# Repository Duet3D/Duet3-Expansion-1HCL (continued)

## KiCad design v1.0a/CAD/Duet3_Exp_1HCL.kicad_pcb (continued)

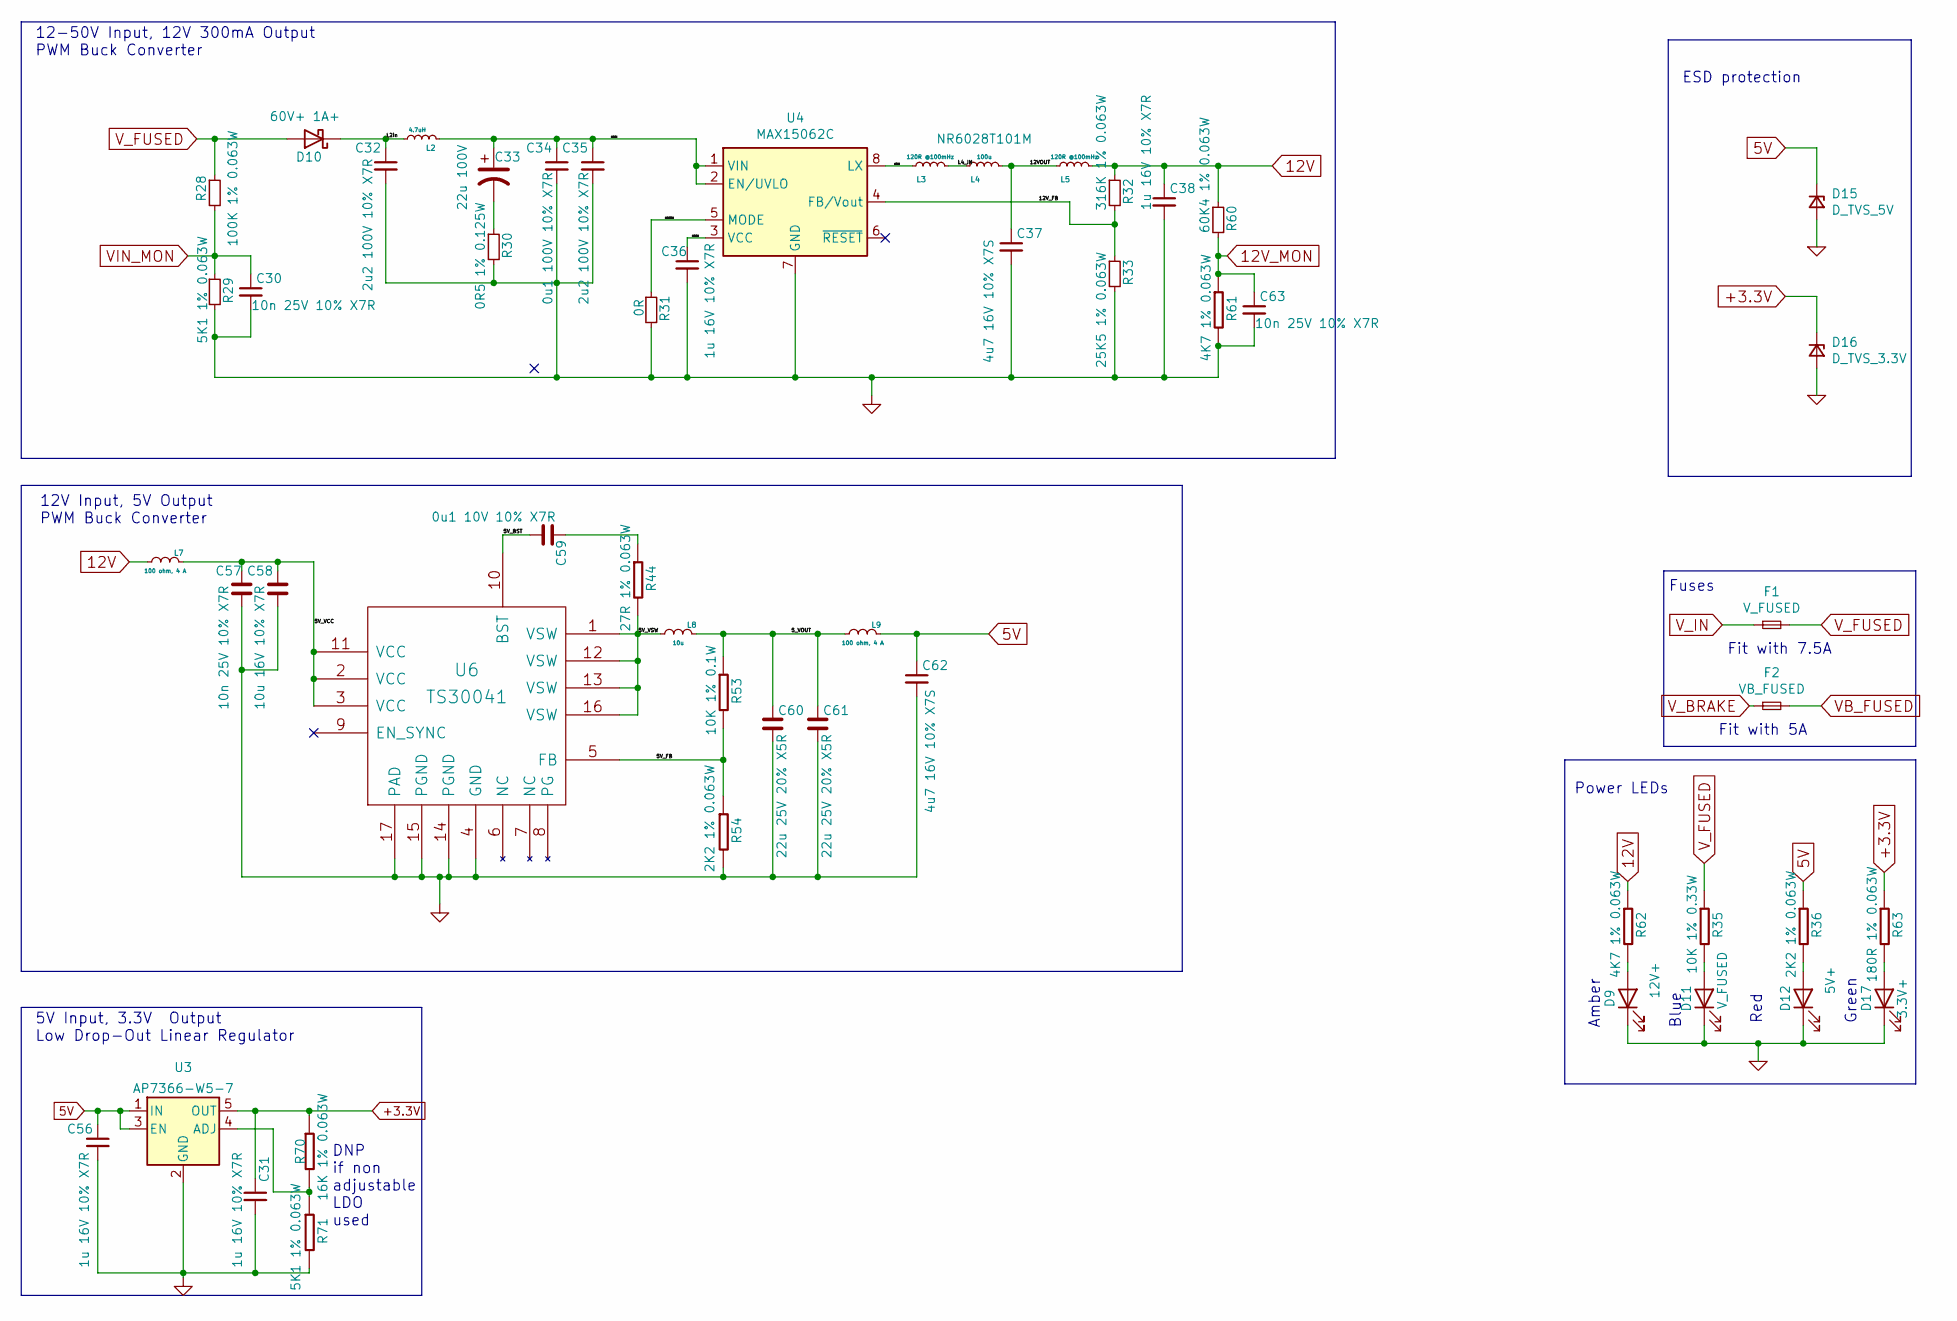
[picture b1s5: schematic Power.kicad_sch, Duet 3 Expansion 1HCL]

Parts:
C30, C57, C63: 10n 25V 10% X7R; C_0402_1005Metric_Wbry; Part Number CL05B103KA5VPNC
C31, C36, C38, C56: 1u 16V 10% X7R; C_0603_1608Metric_Wbry; Part Number CL10B105KO8NNNC
C32, C35: 2u2 100V 10% X7R; C_1210_3225Metric; Part Number CL32B225KCJSNNE
C33: 22u 100V; CP_Elec_8x10; Part Number EEE-2AA220UP or similar
C34: 0u1 100V 10% X7R; C_0603_1608Metric_Wbry; Part Number HMK107B7104MA-T or similar
C37, C62: 4u7 16V 10% X7S; C_1206_3216Metric; Part Number GRM21BR71C475KE51K
C58: 10u 16V 10% X7R; C_0805_2012Metric; Part Number CL21B106KOQNNNE
C59: 0u1 10V 10% X7R; C_0402_1005Metric_Wbry; Part Number CL05B104KP5NNNC
C60, C61: 22u 25V 20% X5R; C_0805_2012Metric; Part Number GRM21BR61E226ME44L
D9: 12V+; LED_0603_1608Metric; Part Number 150060AS75000 or equivalent Amber
D10: 60V+ 1A+; D_SMF; Part Number SS1FH10-M3/H or equivalent
D11: V_FUSED; LED_0603_1608Metric; Part Number 150060BS75000 or equivalent Blue
D12: 5V+; LED_0603_1608Metric; Part Number 150060RS75000 or equivalent Red
D15: D_TVS_5V; DFN1610-2L; Part Number 824032815 or 824031815
D16: D_TVS_3.3V; DFN1610-2L; Part Number 824032813
D17: 3.3V+; LED_0603_1608Metric; Part Number 150060VS75000 or equivalent Green
F1: V_FUSED; MCCQ-122-minibladefuseholder; Part Number Fit with 5A Fuse
F2: VB_FUSED; MCCQ-122-minibladefuseholder; Part Number Fit with 5A Fuse
L2: 4.7uH; L_0805_2012Metric; Part Number MBKK2012T4R7M or CB2012T4R7M or similar
L3, L5: 120R @100mHz; L_0402_1005Metric; Part Number 7427927311 or similar
L4: 100u; L_Taiyo-Yuden_NR-60xx; Rating >0.5A, >0.6A saturation, shielded, <0R8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; Part Number NR6028T101M
L7, L9: 100 ohm, 4 A; L_0805_2012Metric; Part Number 742792025 or MPZ2012S101A or similar
L8: 10u; L_Wuerth_7440405xxxx; Part Number 74404054100 or NR5040T100M
R28: 100K 1% 0.063W; R_0402_1005Metric_Wbry; Part Number RMCF0402FT100K
R29, R71: 5K1 1% 0.063W; R_0402_1005Metric_Wbry; Part Number RMCF0402FT5K10
R30: 0R5 1% 0.125W; R_0402_1005Metric_Wbry; Part Number CSR0402FKR500
R31: 0R; R_0402_1005Metric_Wbry; Part Number RMCF0402ZT0R00
R32: 316K 1% 0.063W; R_0402_1005Metric_Wbry; Part Number RC0402FR-07316KL
R33: 25K5 1% 0.063W; R_0402_1005Metric_Wbry; Part Number AC0402FR-0725K5L
R35: 10K 1% 0.33W; R_0805_2012Metric; Part Number CRGH0805F10K
R36, R54: 2K2 1% 0.063W; R_0402_1005Metric_Wbry; Part Number RK73H1ETTP2201F
R44: 27R 1% 0.063W; R_0402_1005Metric_Wbry; Rating 0.1W+; Part Number CRGCQ0402F27R
R53: 10K 1% 0.1W; R_0402_1005Metric_Wbry; Part Number RK73H1ETTP1002F
R60: 60K4 1% 0.063W; R_0402_1005Metric_Wbry; Part Number RMCF0402FT60K4
R61, R62: 4K7 1% 0.063W; R_0402_1005Metric_Wbry; Part Number RK73H1ETTP4701F
R63: 180R 1% 0.063W; R_0402_1005Metric_Wbry; Part Number RMCF0402FT180R
R70: 16K 1% 0.063W; R_0402_1005Metric_Wbry; Part Number RMCF0402FT16K0
U3: AP7366-W5-7; SOT-23-5; Part Number AP7366-W5-7
U4: MAX15062C; DFN-8_2x2mm_P0.5mm; Part Number MAX15062C
U6: TS30041; QFN-16-1EP_3x3mm_P0.5mm_EP1.8x1.8mm_ThermalVias; Part Number TS30041-M000QFNR

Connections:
5V: C56.1, C62.1, D15.1 (K), L9.1 (A), R36.1, U3.1 (IN), U3.3 (EN); also elsewhere on the board
12V: C38.1, L5.2, L7.2 (B), R32.1, R60.1, R62.1; also elsewhere on the board
12V_MON: C63.1, R60.2, R61.1; also elsewhere on the board
+3.3V: C31.1, D16.1 (K), R63.1, R70.1, U3.5 (OUT); also elsewhere on the board
/Power/5V_BST: C59.2, U6.10 (BST)
/Power/5V_FB: R53.2, R54.1, U6.5 (FB)
/Power/5V_VCC: C57.1, C58.1, L7.1 (A), U6.2 (VCC), U6.3 (VCC), U6.11 (VCC)
/Power/5V_VSW: L8.2 (B), R44.2, U6.1 (VSW), U6.12 (VSW), U6.13 (VSW), U6.16 (VSW)
/Power/5_VOUT: C60.1, C61.1, L8.1 (A), L9.2 (B), R53.1
/Power/12LX: L3.1, U4.8 (LX)
/Power/12MODE: R31.1, U4.5 (MODE)
/Power/12VCC: C36.1, U4.3 (VCC)
/Power/12VIN: C33.1, C34.1, C35.1, L2.2, U4.1 (VIN), U4.2 (EN/UVLO)
/Power/12VOUT: C37.1, L4.2, L5.1
/Power/12V_FB: R32.2, R33.1, U4.4 (FB/Vout)
/Power/L2in: C32.1, D10.1 (K), L2.1
/Power/L4_IN: L3.2, L4.1
GND: C30.2, C31.2, C32.2, C34.2, C35.2, C36.2, C37.2, C38.2, C56.2, C57.2, C58.2, C60.2, C61.2, C62.2, C63.2, D9.1 (K), D11.1 (K), D12.1 (K), D15.2 (A), D16.2 (A), D17.1 (K), R29.2, R30.2, R31.2, R33.2, R54.2, R61.2, R71.2, U3.2 (GND), U4.7 (GND), U6.4 (GND), U6.14 (PGND), U6.15 (PGND), U6.17 (PAD); also elsewhere on the board
unnamed: C33.2, R30.1
unnamed: C59.1, R44.1
unnamed: D9.2 (A), R62.2
unnamed: D11.2 (A), R35.2
unnamed: D12.2 (A), R36.2
unnamed: D17.2 (A), R63.2
unnamed: R70.2, R71.1, U3.4 (ADJ)
VB_FUSED: F2.2; also elsewhere on the board
VIN_MON: C30.1, R28.2, R29.1; also elsewhere on the board
V_BRAKE: F2.1; also elsewhere on the board
V_FUSED: D10.2 (A), F1.2, R28.1, R35.1; also elsewhere on the board
V_IN: F1.1; also elsewhere on the board

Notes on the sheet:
Fit with 7.5A
5V Input, 3.3V Output Low Drop-Out Linear Regulator
12V Input, 5V Output PWM Buck Converter
Power LEDs
Fit with 5A
Fuses
Amber
12-50V Input, 12V 300mA Output PWM Buck Converter
ESD protection
DNP if non adjustable LDO used
Blue
Red
Green

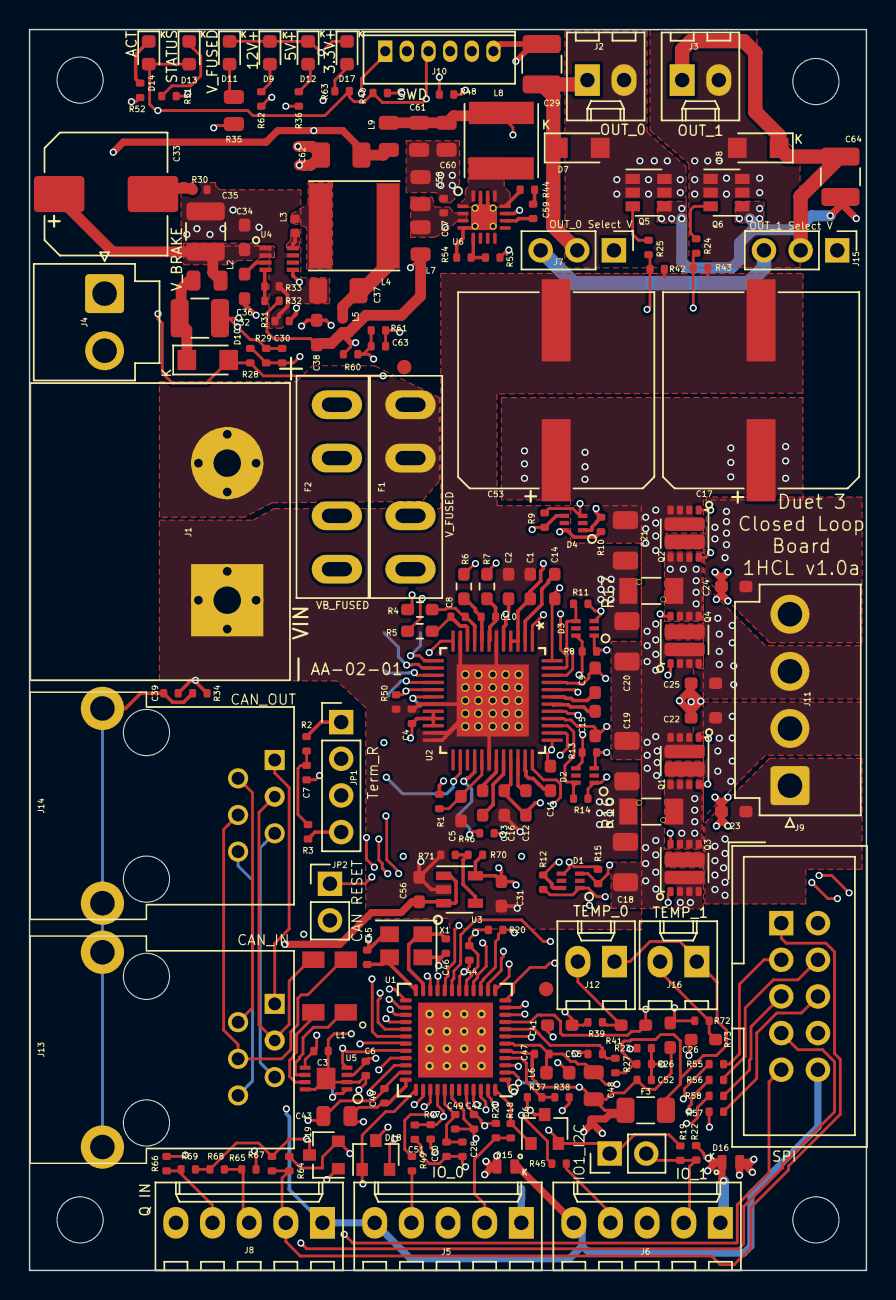
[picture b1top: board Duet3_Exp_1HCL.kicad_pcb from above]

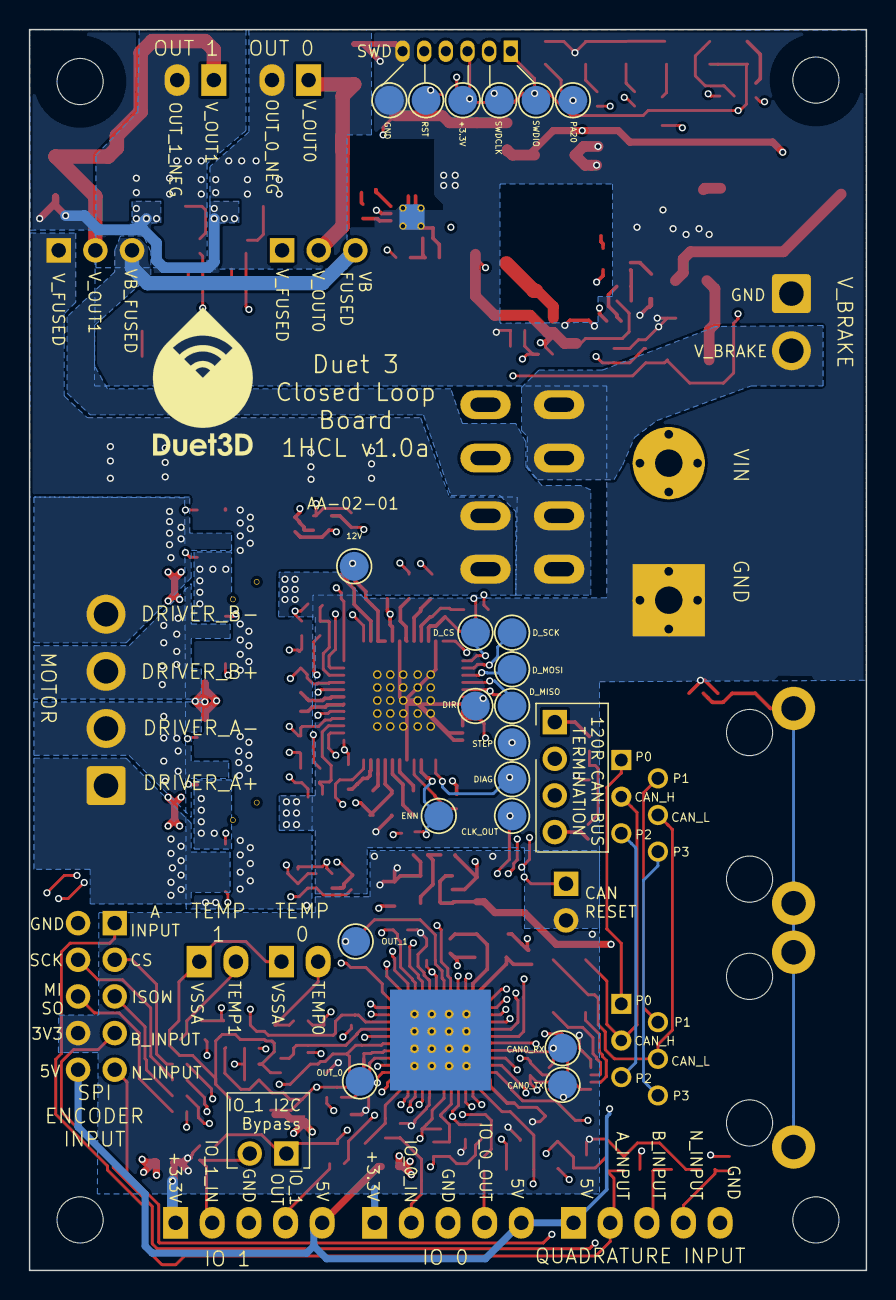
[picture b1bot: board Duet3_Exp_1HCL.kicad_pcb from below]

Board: 4 copper layers, 58.0 x 86.0 mm, 224 parts (21 on the bottom side), 143 nets.

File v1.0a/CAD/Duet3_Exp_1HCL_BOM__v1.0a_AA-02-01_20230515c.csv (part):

"Source:","G:\My Drive\Duet\Duet3\Duet3 Expansion 1HCL\Duet3_Expansion_1HCL_v1.0a-AA-02-01\Duet3_Exp_1HCL.kicad_sch"
"Date:","15/05/2023 18:52:26"
"Tool:","Eeschema (6.0.0)"
"Generator:","C:\Program Files\KiCad\bin\scripting\plugins/bom_csv_grouped_by_value_d3d.py"
"Component Count:","204"

"Collated Components:"

"Item","Value","Qty","LibPart","Footprint","Reference(s)","Datasheet","Frequency","Part Number","Rating"
"1","2u2 16V 10% X5R","4","Device:C_Small","Capacitor_SMD:C_0603_1608Metric_Wbry","C1, C2, C26, C41","~","","CL10A225KO8NNNC",""
"2","0u1 10V 10% X7R","8","Device:C_Small","Capacitor_SMD:C_0402_1005Metric_Wbry","C3, C4, C6, C40, C42, C44, C47, C49","~","","CL05B104KP5NNNC",""
"3","470n 16V 10% X7R","1","Device:C_Small","Capacitor_SMD:C_0603_1608Metric_Wbry","C5","~","","CL10B474KO8NNNC",""
"4","10n 25V 10% X7R","5","Device:C_Small","Capacitor_SMD:C_0402_1005Metric_Wbry","C7, C30, C39, C51, C63","~","","CL05B103KA5VPNC",""
"5","2n2 50V 10% X7R","2","Device:C_Small","Capacitor_SMD:C_0402_1005Metric_Wbry","C8, C10","~","","GCM155R71H222KA37D",""
"6","220n 16V 10% X7R","4","Device:C_Small","Capacitor_SMD:C_0603_1608Metric_Wbry","C9, C11, C14, C15","~","","CL10B224KO8NNNC",""
"7","0u1 50V  10% X7R","1","Device:C_Small","Capacitor_SMD:C_0603_1608Metric_Wbry","C12","~","","CL10B104KB8NNNC",""
"8","22n 100V 10% X7R","1","Device:C_Small","Capacitor_SMD:C_0603_1608Metric_Wbry","C13","~","","C0603C223K1RACTU",""
"9","0u1 100V 10% X7R","2","Device:C_Small","Capacitor_SMD:C_0603_1608Metric_Wbry","C16, C34","~","","HMK107B7104MA-T or similar",""
"10","220u 63V","2","Device:CP1_Small","Capacitor_SMD:CP_Elec_12.5x14","C17, C53","","","865060762009",""
"11","220n 100V 10% X7R","4","Device:C_Small","Capacitor_SMD:C_1206_3216Metric","C18, C19, C20, C21","~","","C3216X7R2A224K115AA",""
"12","1n 100V 10% X7R","4","Device:C_Small","Capacitor_SMD:C_0603_1608Metric_Wbry","C22, C23, C24, C25","~","","CGA3E2X7R2A102K080AA",""
"13","2u2 6.3V 10% X7R","4","Device:C_Small","Capacitor_SMD:C_0402_1005Metric_Wbry","C28, C50, C52, C55","~","","CC0603KRX7R5BB225",""
"14","2u2 100V 10% X7R","4","Device:C_Small","Capacitor_SMD:C_1210_3225Metric","C29, C32, C35, C64","~","","CL32B225KCJSNNE",""
"15","1u 16V 10% X7R","4","Device:C_Small","Capacitor_SMD:C_0603_1608Metric_Wbry","C31, C36, C38, C56","~","","CL10B105KO8NNNC",""
"16","22u 100V","1","Device:CP1","Capacitor_SMD:CP_Elec_8x10","C33","","","EEE-2AA220UP or similar",""
"17","4u7 16V 10% X7S","2","Device:C_Small","Capacitor_SMD:C_1206_3216Metric","C37, C62","~","","GRM21BR71C475KE51K",""
"18","10u 16V 10% X7R","2","Device:C_Small","Capacitor_SMD:C_0805_2012Metric","C43, C48","~","","CL21B106KOQNNNE",""
"19","22p 16V 5% C0G,NP0","2","Device:C_Small","Capacitor_SMD:C_0402_1005Metric_Wbry","C45, C46","~","","C0402C220J4GACTU",""
"20","10n 25V 10% X7R","1","Duet3:C_SMALL","Capacitor_SMD:C_0402_1005Metric_Wbry","C57","","","CL05B103KA5VPNC",""
"21","10u 16V 10% X7R","1","Duet3:C_SMALL","Capacitor_SMD:C_0805_2012Metric","C58","","","CL21B106KOQNNNE",""
"22","0u1 10V 10% X7R","1","Duet3:C_SMALL","Capacitor_SMD:C_0402_1005Metric_Wbry","C59","","","CL05B104KP5NNNC",""
"23","22u 25V 20% X5R","2","Duet3:C_SMALL","Capacitor_SMD:C_0805_2012Metric","C60, C61","","","GRM21BR61E226ME44L",""
"24","BAT40V","4","Diode:BAT40V","Package_TO_SOT_SMD:SOT-563","D1, D2, D3, D4","","","BAT40V-7",""
"25","BAT54C","3","Diode:BAT54C","Package_TO_SOT_SMD:SOT-23","D6, D18, D19","http://www.diodes.com/_files/datasheets/ds11005.pdf","","BAT54CLT1G",""
"26","60V+ 1A+","3","Device:D_Schottky","Diode_SMD:D_SMF","D7, D8, D10","~","","SS1FH10-M3/H or equivalent",""
"27","12V+","1","Device:LED","LED_SMD:LED_0603_1608Metric","D9","~","","150060AS75000 or equivalent Amber",""
"28","V_FUSED","1","Device:LED","LED_SMD:LED_0603_1608Metric","D11","~","","150060BS75000  or equivalent Blue",""
"29","5V+","1","Device:LED","LED_SMD:LED_0603_1608Metric","D12","~","","150060RS75000 or equivalent Red",""
"30","STATUS","1","Device:LED","LED_SMD:LED_0603_1608Metric","D13","~","","150060RS75000 or equivalent Red",""
"31","ACT","1","Device:LED","LED_SMD:LED_0603_1608Metric","D14","~","","150060VS75000  or equivalent Green",""
"32","D_TVS_5V","1","Device:D_Zener_Small","Diode_SMD:DFN1610-2L","D15","~","","824032815 or 824031815",""
"33","D_TVS_3.3V","1","Device:D_Zener_Small","Diode_SMD:DFN1610-2L","D16","~","","824032813",""
"34","3.3V+","1","Device:LED","LED_SMD:LED_0603_1608Metric","D17","~","","150060VS75000  or equivalent Green",""
"35","V_FUSED","1","Device:Fuse_Small","complib:MCCQ-122-minibladefuseholder","F1","~","","Fit with 5A Fuse",""
"36","VB_FUSED","1","Device:Fuse_Small","complib:MCCQ-122-minibladefuseholder","F2","~","","Fit with 5A Fuse",""
"37","VSSA FUSE","1","Device:Fuse","Fuse:Fuse_1206_3216Metric","F3","~","","0ZCJ0020FF2E",""
"38","VIN","1","Connector_Generic:Conn_01x02","complib:screwt-barrier-9.5mm-1x2","J1","~",""," HB950-9.50-2P",""
"39","OUT_0","1","Connector_Generic:Conn_01x02","Connector_Molex:Wurth_61900211121-1x02_P2.54mm_Vertical-(Molex_KK-254_AE-6410-02Acompatible)","J2","~","","61900211121",""
"40","OUT_1","1","Connector_Generic:Conn_01x02","Connector_Molex:Wurth_61900211121-1x02_P2.54mm_Vertical-(Molex_KK-254_AE-6410-02Acompatible)","J3","~","","61900211121",""
"41","V_BRAKE","1","Connector_Generic:Conn_01x02","Connector_JST:JST_VH_B2P-VH_1x02_P3.96mm_Vertical","J4","~","","B2P-VH(LF)(SN)",""
"42","IO_0","1","Connector_Generic:Conn_01x05","Connector_Molex:Wurth_61900511121-1x05_P2.54mm_Vertical(Molex_KK-254_AE-6410-05A_Compatibe)","J5","~","","61900511121",""
"43","IO_1","1","Connector_Generic:Conn_01x05","Connector_Molex:Wurth_61900511121-1x05_P2.54mm_Vertical(Molex_KK-254_AE-6410-05A_Compatibe)","J6","~","","61900511121",""
"44","OUT_0 Select V","1","Connector_Generic:Conn_01x03","Connector_PinHeader_2.54mm:PinHeader_1x03_P2.54mm_Vertical","J7","~","","THS-03-R",""
"45","Q IN","1","Connector_Generic:Conn_01x05","Connector_Molex:Wurth_61900511121-1x05_P2.54mm_Vertical(Molex_KK-254_AE-6410-05A_Compatibe)","J8","~","","61900511121",""
"46","SPI","1","Connector_Generic:Conn_02x05_Odd_Even","Connector_IDC:IDC-Header_2x05_P2.54mm_Vertical","J9","~","","61201021621",""
"47","SWD","1","Connector_Generic:Conn_01x06","complib:JST_ZH_1x06_P1.5_B6B-ZR-SM4-TF","J10","~","","B6B-ZR(LF)(SN) ",""
"48","DRIVER","1","Connector_Generic:Conn_01x04","Connector_JST:JST_VH_B4P-VH_1x04_P3.96mm_Vertical","J11","~","","B4P-VH(LF)(SN)",""
"49","TEMP_0","1","Connector_Generic:Conn_01x02","Connector_Molex:Wurth_61900211121-1x02_P2.54mm_Vertical-(Molex_KK-254_AE-6410-02Acompatible)","J12","~","","61900511121",""
"50","CAN_IN","1","Duet3:RJ12-Connector_Specialized","complib:RJ11_6P6C_half_shield","J13","","","Wurth 615 006 143 421 or equivalent",""
"51","CAN_OUT","1","Duet3:RJ12-Connector_Specialized","complib:RJ11_6P6C_half_shield","J14","","","Wurth 615 006 143 421 or equivalent",""
"52","OUT_1 Select V","1","Connector_Generic:Conn_01x03","Connector_PinHeader_2.54mm:PinHeader_1x03_P2.54mm_Vertical","J15","~","","THS-03-R",""
"53","TEMP_1","1","Connector_Generic:Conn_01x02","Connector_Molex:Wurth_61900211121-1x02_P2.54mm_Vertical-(Molex_KK-254_AE-6410-02Acompatible)","J16","~","","61900511121",""
"54","Term_R","1","Duet3:Jumper_4_Open","Connector_PinHeader_2.54mm:PinHeader_1x04_P2.54mm_Vertical","JP1","~","","THS-04-R",""
"55","CAN RESET","1","Device:Jumper_NO_Small","Connector_PinHeader_2.54mm:PinHeader_1x02_P2.54mm_Vertical","JP2","","","THS-02-R",""
"56","IO1_I2C","1","Device:Jumper_NO_Small","Connector_PinHeader_2.54mm:PinHeader_1x02_P2.54mm_Vertical","JP3","","","THS-02-R",""
"57","CM Choke","1","Duet3:L_Coupled_v2","complib:Wurth_CM_Choke_1812_744235nnn","L1","~","","744235110",""
"58","4.7uH","1","Device:L_Small","Inductor_SMD:L_0805_2012Metric","L2","~","","MBKK2012T4R7M or CB2012T4R7M or similar",""
"59","120R @100mHz","2","Device:L_Small","Inductor_SMD:L_0402_1005Metric","L3, L5","~","","7427927311 or similar",""
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
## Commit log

2022-06-17 Schematic and STEP File for Duet 3 1HCL
2023-09-12 Update LICENSE
2023-09-28 v1.0a
2023-10-17 updated readme links
2025-01-07 v2.0 Step
